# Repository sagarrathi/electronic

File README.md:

# PublicProjects
All projects which were success or failure. Learned from both of them.

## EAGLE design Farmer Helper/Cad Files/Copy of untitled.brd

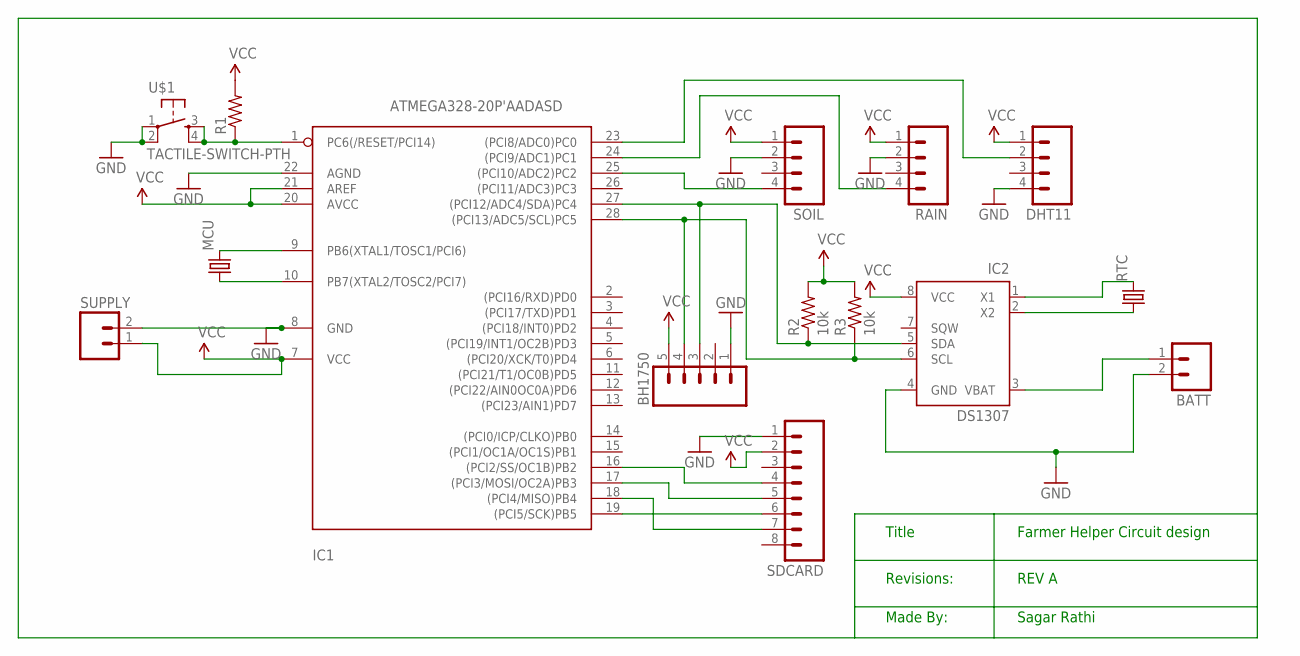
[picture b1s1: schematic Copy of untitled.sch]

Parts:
BATT: M02PTH3; 1X02_LONGPADS
BH1750: M05LOCK_LONGPADS; 1X05_LOCK_LONGPADS
DHT11: M04LONGPADS; 1X04_LONGPADS
IC1: ATMEGA328-20P'AADASD; DIL28-3
IC2: DS1307; DIP-8
MCU: CRYSTALTC38H; TC38H
R1: RESISTORAXIAL-0.3; AXIAL-0.3
R2, R3: 10k; AXIAL-0.3
RAIN: M04LONGPADS; 1X04_LONGPADS
RTC: CRYSTALTC26H_EZ; TC26HEZ
SDCARD: M08LONGPADS; 1X08_LONGPADS
SOIL: M04LONGPADS; 1X04_LONGPADS
SUPPLY: M02PTH3; 1X02_LONGPADS
U$1: TACTILE-SWITCH-PTH; TAC-SWITCH-PTH

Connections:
GND: BATT.2, BH1750.1, DHT11.4, IC1.8 (GND), IC1.22 (AGND), IC2.4 (GND), RAIN.2, SDCARD.1, SOIL.2, SUPPLY.2, U$1.1, U$1.2
unnamed: IC1.1 (PC6(/RESET/PCI14)), R1.P$1 (1), U$1.3, U$1.4
unnamed: IC1.9 (PB6(XTAL1/TOSC1/PCI6)), MCU.2
unnamed: IC1.10 (PB7(XTAL2/TOSC2/PCI7)), MCU.1
unnamed: IC1.25 ((PCI10/ADC2)PC2), SOIL.4
unnamed: IC1.24 ((PCI9/ADC1)PC1), RAIN.4
unnamed: DHT11.2, IC1.23 ((PCI8/ADC0)PC0)
unnamed: IC2.1 (X1), RTC.2
unnamed: IC2.2 (X2), RTC.1
unnamed: BATT.1, IC2.3 (VBAT)
unnamed: BH1750.4, IC1.28 ((PCI13/ADC5/SCL)PC5), IC2.6 (SCL), R3.P$1 (1)
unnamed: BH1750.3, IC1.27 ((PCI12/ADC4/SDA)PC4), IC2.5 (SDA), R2.P$1 (1)
unnamed: IC1.16 ((PCI2/SS/OC1B)PB2), SDCARD.4
unnamed: IC1.17 ((PCI3/MOSI/OC2A)PB3), SDCARD.5
unnamed: IC1.19 ((PCI5/SCK)PB5), SDCARD.6
unnamed: IC1.18 ((PCI4/MISO)PB4), SDCARD.7
VCC: BH1750.5, DHT11.1, IC1.7 (VCC), IC1.20 (AVCC), IC1.21 (AREF), IC2.8 (VCC), R1.P$2 (2), R2.P$2 (2), R3.P$2 (2), RAIN.1, SDCARD.2, SOIL.1, SUPPLY.1

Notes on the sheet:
Farmer Helper Circuit design
Title
Revisions:
REV A
Made By:
Sagar Rathi

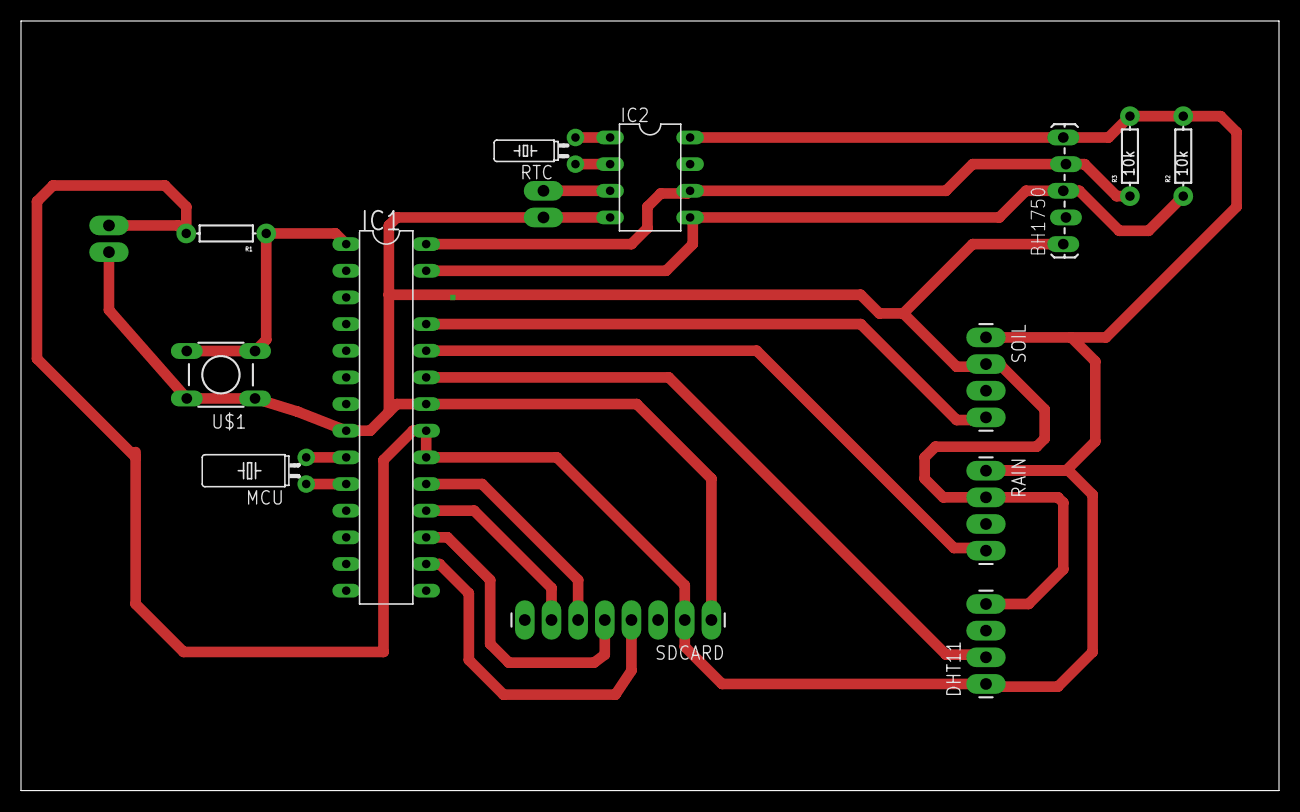
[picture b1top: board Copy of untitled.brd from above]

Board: 2 copper layers, 119.9 x 73.3 mm, 15 parts (0 on the bottom side), 17 nets.

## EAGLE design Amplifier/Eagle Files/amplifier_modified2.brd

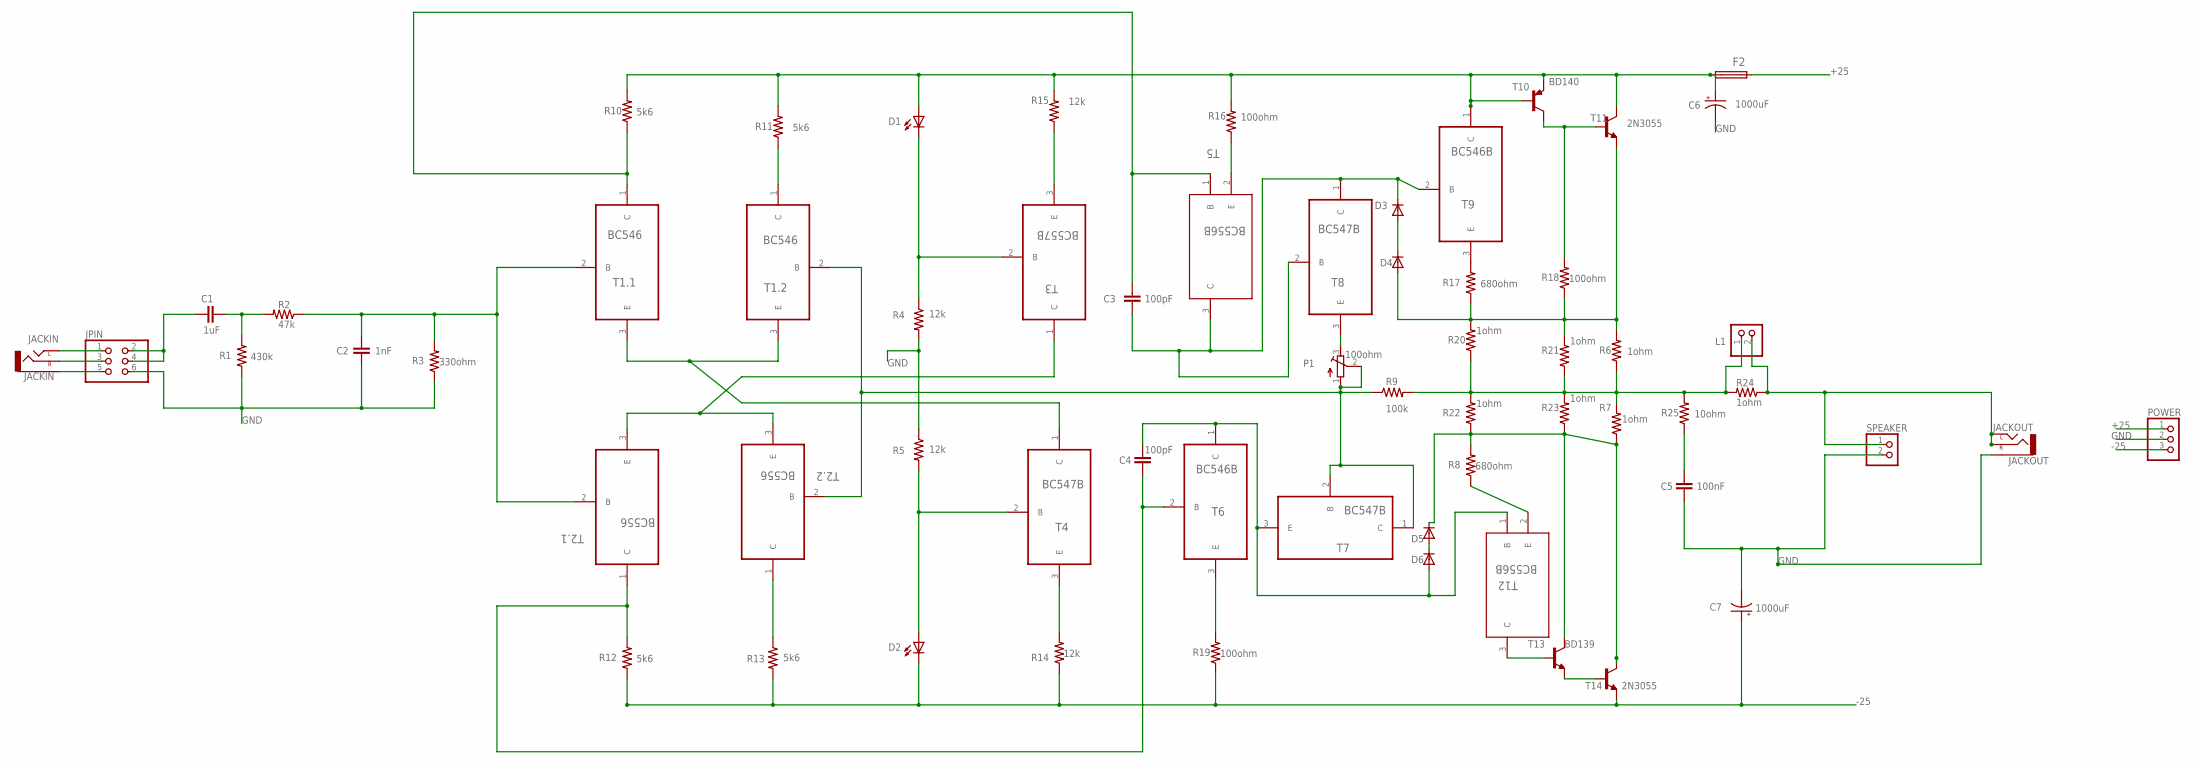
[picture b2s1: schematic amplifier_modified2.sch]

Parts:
C1: 1uF; CAP-PTH-5MM
C2: 1nF; CAP-PTH-5MM
C3, C4: 100pF; C5B3
C5: 100nF; C5B3
C6, C7: 1000uF; E5-6
D1, D2: LED5MM
D3, D4, D5, D6: 1N4148DO35-10; DO35-10
F2: FUSEBLANK_5X20MM; FUSE_HOLDER_5X20MM
JACKIN: JACKIN; STEREOJACK2.5MM_STEREOJACK2.5MM
JACKOUT: JACKOUT; STEREOJACK2.5MM_STEREOJACK2.5MM
JPIN: PINHD-2X3/90; 2X03/90
L1: PINHD-1X2/90; 1X02/90
P1: 100ohm; RTRIM74X
POWER: PINHD-1X3/90; 1X03/90
R1: 430k; AXIAL-0.8
R2: 47k; AXIAL-0.8
R3: 330ohm; AXIAL-0.8
R4, R5, R14, R15: 12k; AXIAL-0.8
R6, R7, R20, R21, R22, R23, R24: 1ohm; AXIAL-0.8
R8, R17: 680ohm; AXIAL-0.8
R9: 100k; AXIAL-0.8
R10, R11, R12, R13: 5k6; AXIAL-0.8
R16, R18, R19: 100ohm; AXIAL-0.8
R25: 10ohm; AXIAL-0.8
SPEAKER: PINHD-1X2/90; 1X02/90
T1.1, T1.2: BC546; TO127P254X732-3
T2.1, T2.2: BC556; TO127P254X732-3
T3: BC557B; TO127P254X732-3
T4, T7, T8: BC547B; TO127P254X732-3
T5, T12: BC556B; SOT95P240X110-3N; MPN BC857A
T6, T9: BC546B; TO127P254X732-3
T10: BD140; TO126
T11, T14: 2N3055; TO3
T13: BD139; TO126

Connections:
+25: F2.2, POWER.1
-25: C7.+, D2.K (C), POWER.3, R12.P$1 (1), R13.P$2 (2), R14.P$1 (1), R19.P$1 (1), T14.E
GND: C2.1, C5.1, C6.-, C7.-, JACKOUT.RING1 (SLEEVE), JPIN.6, POWER.2, R1.P$1 (1), R3.P$1 (1), R4.P$2 (2), R5.P$1 (1), SPEAKER.2
unnamed: JACKIN.SHIELD (LEFT), JPIN.1
unnamed: C1.2, R1.P$2 (2), R2.P$2 (2)
unnamed: C2.2, R2.P$1 (1), R3.P$2 (2), T1.1.2 (B), T2.1.2 (B)
unnamed: P1.3 (E), T8.3 (E)
unnamed: T2.1.3 (E), T2.2.3 (E), T3.1 (C)
unnamed: P1.1 (A), P1.2 (S), R9.P$1 (1), T1.2.2 (B), T2.2.2 (B), T7.1 (C), T7.2 (B)
unnamed: C3.2, R10.P$1 (1), T1.1.1 (C), T5.1 (B)
unnamed: T1.1.3 (E), T1.2.3 (E), T4.1 (C)
unnamed: C4.1, R12.P$2 (2), T2.1.1 (C), T6.2 (B)
unnamed: R11.P$1 (1), T1.2.1 (C)
unnamed: C5.2, R25.P$1 (1)
unnamed: D1.K (C), R4.P$1 (1), T3.2 (B)
unnamed: R13.P$1 (1), T2.2.1 (C)
unnamed: D2.A, R5.P$2 (2), T4.2 (B)
unnamed: R14.P$2 (2), T4.3 (E)
unnamed: R15.P$1 (1), T3.3 (E)
unnamed: R16.P$1 (1), T5.2 (E)
unnamed: C3.1, D3.C, T5.3 (C), T8.1 (C), T8.2 (B), T9.2 (B)
unnamed: R19.P$2 (2), T6.3 (E)
unnamed: C4.2, D6.A, T6.1 (C), T7.3 (E), T12.1 (B)
unnamed: JACKIN.RING1 (SLEEVE), JPIN.5
unnamed: JACKIN.TIP (RIGHT), JPIN.3
unnamed: D5.A, D6.C
unnamed: R17.P$2 (2), T9.3 (E)
unnamed: D3.A, D4.C
unnamed: D4.A, R6.P$2 (2), R17.P$1 (1), R18.P$1 (1), R20.P$2 (2), R21.P$2 (2), T11.E
unnamed: C6.+, D1.A, F2.1, R10.P$2 (2), R11.P$2 (2), R15.P$2 (2), R16.P$2 (2), T9.1 (C), T10.1 (E), T10.3 (B), T11.C, T11.C/ (C)
unnamed: R18.P$2 (2), T10.2 (C), T11.B
unnamed: R8.P$1 (1), T12.2 (E)
unnamed: T12.3 (C), T13.3 (B)
unnamed: T13.1 (E), T14.B
unnamed: JACKOUT.SHIELD (LEFT), JACKOUT.TIP (RIGHT), L1.2, R24.P$1 (1), SPEAKER.1
unnamed: L1.1, R6.P$1 (1), R7.P$2 (2), R9.P$2 (2), R20.P$1 (1), R21.P$1 (1), R22.P$2 (2), R23.P$2 (2), R24.P$2 (2), R25.P$2 (2)
unnamed: D5.C, R7.P$1 (1), R8.P$2 (2), R22.P$1 (1), R23.P$1 (1), T13.2 (C), T14.C, T14.C/ (C)
unnamed: C1.1, JPIN.2, JPIN.4

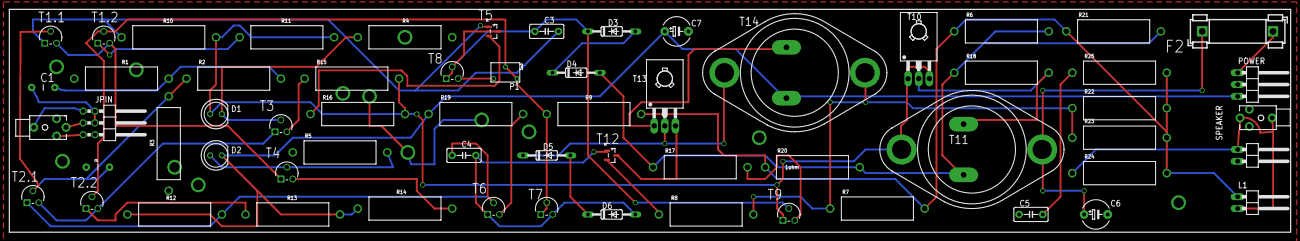
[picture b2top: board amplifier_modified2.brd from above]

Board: 2 copper layers, 275.6 x 47.9 mm, 62 parts (0 on the bottom side), 38 nets.

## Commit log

2018-11-21 Elec repo first commit

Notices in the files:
parts and their libraries:
SparkFun-Resistors: Licensing: CC v3.0 Share-Alike You are welcome to use this library for commercial purposes.
SparkFun-Connectors: Licensing: Creative Commons ShareAlike 4.0 International - https://creativecommons.org/licenses/by-sa/4.0
